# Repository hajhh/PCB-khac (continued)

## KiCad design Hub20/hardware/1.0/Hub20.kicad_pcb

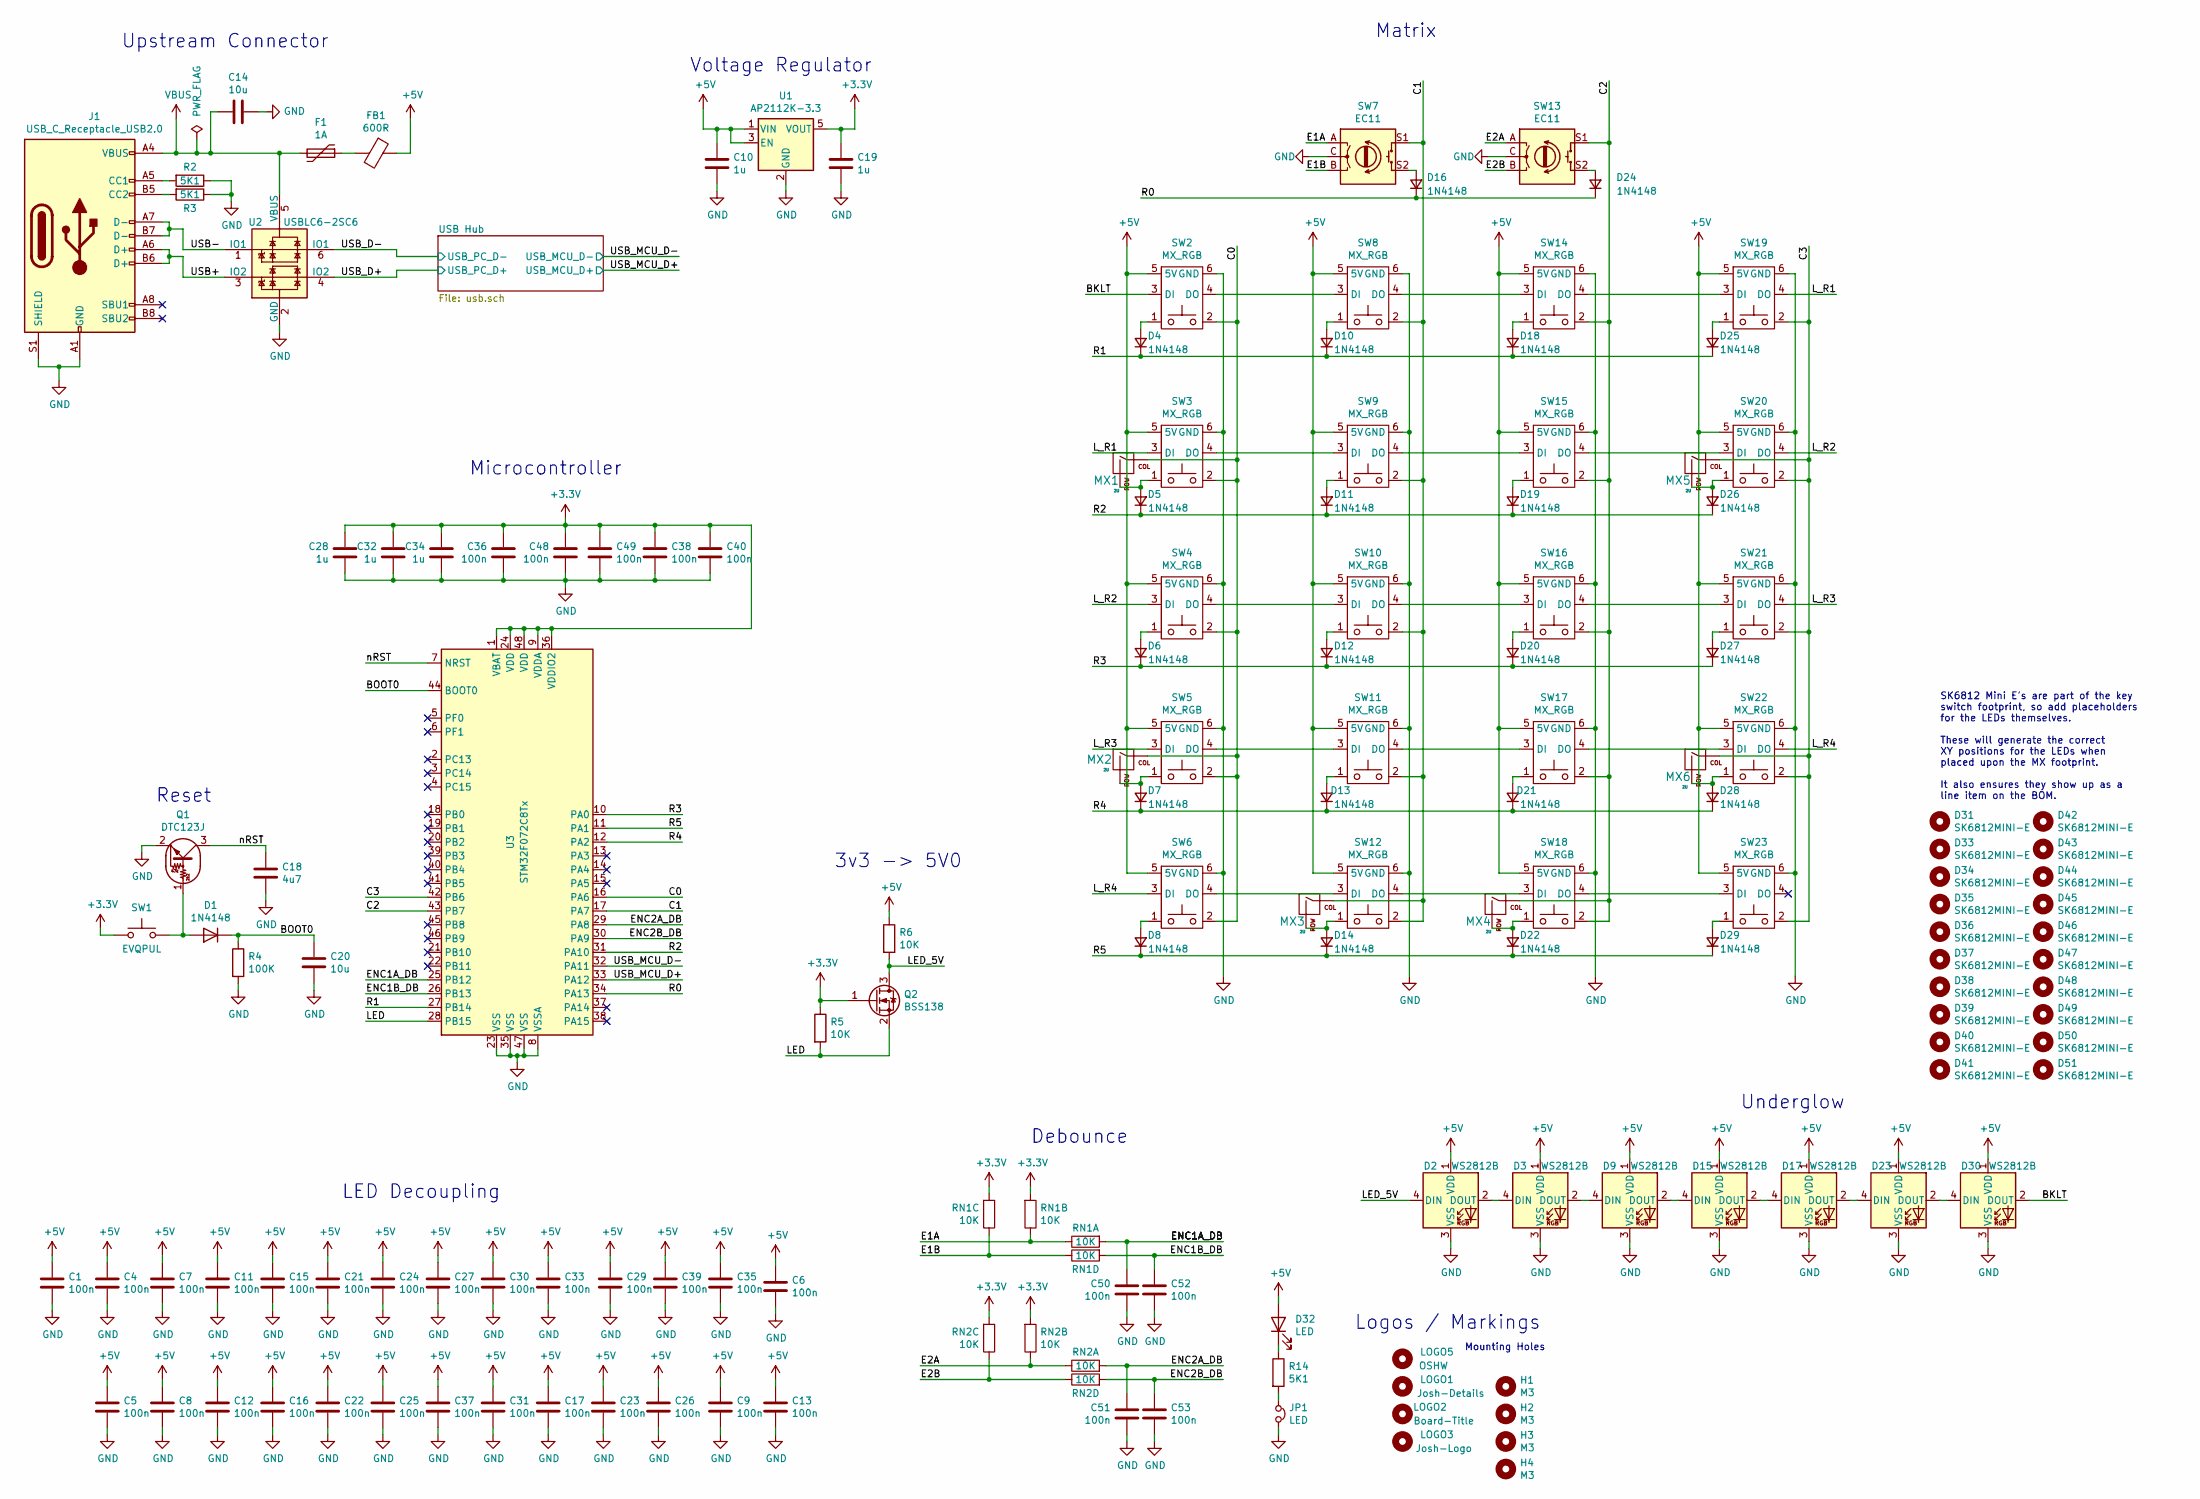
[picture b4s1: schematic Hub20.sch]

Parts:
C1, C4, C5, C6, C7, C8, C9, C11, C12, C13, C15, C16, C17, C21, C22, C23, C24, C25, C26, C27, C29, C30, C31, C33, C35, C36, C37, C38, C39, C40, C48, C49, C50, C51, C52, C53: 100n; C_0603_1608Metric; MPN CL10B104KB8NNNC; DigiKey 1276-1000-1-ND
C10, C19, C28, C32, C34: 1u; C_0603_1608Metric; MPN CL10A105MP8NNNC; DigiKey 1276-1866-1-ND
C14, C20: 10u; C_0603_1608Metric; MPN CL10A106MP8NNNC; DigiKey 1276-1871-1-ND
C18: 4u7; C_0603_1608Metric; MPN CL10A475MP8NNNC; DigiKey 1276-1905-1-ND
D1, D4, D5, D6, D7, D8, D10, D11, D12, D13, D14, D16, D18, D19, D20, D21, D22, D24, D25, D26, D27, D28, D29: 1N4148; D_SOD-123; MPN 1N4148W-7-F; DigiKey 1N4148W-FDICT-ND
D2, D3, D9, D15, D17, D23, D30: WS2812B; LED_WS2812B_PLCC4_5.0x5.0mm_P3.2mm; MPN WS2812B; DigiKey 1528-1104-ND
D31, D33, D34, D35, D36, D37, D38, D39, D40, D41, D42, D43, D44, D45, D46, D47, D48, D49, D50, D51: SK6812MINI-E; DUMMY_SK6812MINI-E; MPN SK6812MINI-E
D32: LED; LED_0603_1608Metric; MPN OSK40603C1E; LCSC C268294
F1: 1A; Fuse_0805_2012Metric; MPN 0805L100WR; DigiKey F2774CT-ND
FB1: 600R; Ferrite_Bead_0603; MPN BLM18KG601SN1D; DigiKey 490-5258-1-ND
H1, H2, H3, H4: M3; MountingHole_3.2mm_M3
J1: USB_C_Receptacle_USB2.0; USB_C_U262-161N-4BVC11; MPN U262-161N-4BVC11; LCSC C319148
JP1: LED; SolderJumper-2_P1.3mm_Bridged_RoundedPad1.0x1.5mm
LOGO1: Josh-Details; josh-details
LOGO2: Board-Title; board-title
LOGO3: Josh-Logo; josh-johnson-logo-11x2
LOGO5: OSHW; OSHW-Logo2_9.8x8mm_Mask
MX1, MX2: 2U; MXOnly-2U-NoLED-3PIN
MX3, MX4, MX5, MX6: 2U; MXOnly-2U-ReversedStabilizers-NoLED-3PIN
Q1: DTC123J; SOT-23; MPN DTC123JKAT146; DigiKey DTC123JKAT146CT-ND
Q2: BSS138; SOT-23; MPN BSS138; DigiKey BSS138CT-ND
R2, R3, R14: 5K1; R_0603_1608Metric; MPN CR0603-JW-512ELF; DigiKey 118-CR0603-JW-512ELFCT-ND
R4: 100K; R_0603_1608Metric; MPN CR0603-JW-104ELF; DigiKey CR0603-JW-104ELFCT-ND
R5, R6: 10K; R_0603_1608Metric; MPN CR0603-JW-103ELF; DigiKey CR0603-JW-103ELFCT-ND
RN1, RN2: 10K; R_Array_Convex_4x0603; MPN RAVF164DJT10K0; DigiKey RAVF164DJT10K0CT-ND
SW1: EVQPUL; Panasonic_EVQPUL_EVQPUC; MPN EVQ-PUL02K; DigiKey P10853SCT-ND
SW2, SW3, SW4, SW5, SW6, SW8, SW9, SW10, SW11, SW12, SW14, SW15, SW16, SW17, SW18, SW19, SW20, SW21, SW22, SW23: MX_RGB; MX_KEYSWITCH_RGB
SW7, SW13: EC11; RotaryEncoder_Alps_EC11E-Switch_Vertical_H20mm_CircularMoun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; MPN PEC11L-4120F-S0020; DigiKey PEC11L-4120F-S0020-ND
U1: AP2112K-3.3; SOT-23-5; MPN AP2112K-3.3TRG1; DigiKey AP2112K-3.3TRG1DICT-ND
U2: USBLC6-2SC6; SOT-23-6; MPN USBLC6-2SC6; DigiKey 497-5235-1-ND
U3: STM32F072C8Tx; LQFP-48_7x7mm_P0.5mm; MPN STM32F072C8T6; DigiKey 497-17359-1-ND

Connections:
+3V3: C19.1, C28.1, C32.1, C34.1, C36.1, C38.1, C40.1, C48.1, C49.1, Q2.1 (G), R5.1, RN1.2, RN1.3, RN2.2, RN2.3, SW1.1, U1.5 (VOUT), U3.1 (VBAT), U3.9 (VDDA), U3.24 (VDD), U3.36 (VDDIO2), U3.48 (VDD)
/BKLT: D30.2 (DOUT), SW2.3 (DI)
/BOOT0: C20.1, D1.1 (K), R4.1, U3.44 (BOOT0)
/C0: MX1.1 (COL), MX2.1 (COL), SW2.2, SW3.2, SW4.2, SW5.2, SW6.2, U3.16 (PA6)
/C1: MX3.1 (COL), SW7.S1, SW8.2, SW9.2, SW10.2, SW11.2, SW12.2, U3.17 (PA7)
/C2: MX4.1 (COL), SW13.S1, SW14.2, SW15.2, SW16.2, SW17.2, SW18.2, U3.43 (PB7)
/C3: MX5.1 (COL), MX6.1 (COL), SW19.2, SW20.2, SW21.2, SW22.2, SW23.2, U3.42 (PB6)
/E1A: RN1.5, RN1.6, SW7.A
/E1B: RN1.7, RN1.8, SW7.B
/E2A: RN2.5, RN2.6, SW13.A
/E2B: RN2.7, RN2.8, SW13.B
/ENC1A_DB: C50.1, RN1.4, U3.25 (PB12)
/ENC1B_DB: C52.1, RN1.1, U3.26 (PB13)
/ENC2A_DB: C51.1, RN2.4, U3.29 (PA8)
/ENC2B_DB: C53.1, RN2.1, U3.30 (PA9)
/LED: Q2.2 (S), R5.2, U3.28 (PB15)
/LED_5V: D2.4 (DIN), Q2.3 (D), R6.2
/L_R1: SW3.3 (DI), SW19.4 (DO)
/L_R2: SW4.3 (DI), SW20.4 (DO)
/L_R3: SW5.3 (DI), SW21.4 (DO)
/L_R4: SW6.3 (DI), SW22.4 (DO)
/R0: D16.1 (K), D24.1 (K), U3.34 (PA13)
/R1: D4.1 (K), D10.1 (K), D18.1 (K), D25.1 (K), U3.27 (PB14)
/R2: D5.1 (K), D11.1 (K), D19.1 (K), D26.1 (K), U3.31 (PA10)
/R3: D6.1 (K), D12.1 (K), D20.1 (K), D27.1 (K), U3.10 (PA0)
/R4: D7.1 (K), D13.1 (K), D21.1 (K), D28.1 (K), U3.12 (PA2)
/R5: D8.1 (K), D14.1 (K), D22.1 (K), D29.1 (K), U3.11 (PA1)
/USB+: J1.A6 (D+), J1.B6 (D+), U2.3 (IO2)
/USB-: J1.A7 (D-), J1.B7 (D-), U2.1 (IO1)
/USB_D+: U2.4 (IO2); also elsewhere on the board
/USB_D-: U2.6 (IO1); also elsewhere on the board
/USB_MCU_D+: U3.33 (PA12); also elsewhere on the board
/USB_MCU_D-: U3.32 (PA11); also elsewhere on the board
GND: C1.2, C4.2, C5.2, C6.2, C7.2, C8.2, C9.2, C10.2, C11.2, C12.2, C13.2, C14.2, C15.2, C16.2, C17.2, C18.2, C19.2, C20.2, C21.2, C22.2, C23.2, C24.2, C25.2, C26.2, C27.2, C28.2, C29.2, C30.2, C31.2, C32.2, C33.2, C34.2, C35.2, C36.2, C37.2, C38.2, C39.2, C40.2, C48.2, C49.2, C50.2, C51.2, C52.2, C53.2, D2.3 (VSS), D3.3 (VSS), D9.3 (VSS), D15.3 (VSS), D17.3 (VSS), D23.3 (VSS), D30.3 (VSS), J1.A1 (GND), J1.A12 (GND), J1.B1 (GND), J1.B12 (GND), J1.S1 (SHIELD), JP1.2, Q1.2 (E), R2.1, R3.1, R4.2, SW2.6 (GND), SW3.6 (GND), SW4.6 (GND), SW5.6 (GND), SW6.6 (GND), SW7.C, SW8.6 (GND), SW9.6 (GND), SW10.6 (GND), SW11.6 (GND), SW12.6 (GND), SW13.C, SW14.6 (GND), SW15.6 (GND), SW16.6 (GND), SW17.6 (GND), SW18.6 (GND), SW19.6 (GND), SW20.6 (GND), SW21.6 (GND), SW22.6 (GND), SW23.6 (GND), U1.2 (GND), U2.2 (GND), U3.8 (VSSA), U3.23 (VSS), U3.35 (VSS), U3.47 (VSS); also elsewhere on the board
unnamed: D1.2 (A), Q1.1 (B), SW1.2
unnamed: D2.2 (DOUT), D3.4 (DIN)
unnamed: D3.2 (DOUT), D9.4 (DIN)
unnamed: D4.2 (A), SW2.1
unnamed: D5.2 (A), MX1.2 (ROW), SW3.1
unnamed: D6.2 (A), SW4.1
unnamed: D7.2 (A), MX2.2 (ROW), SW5.1
unnamed: D8.2 (A), SW6.1
unnamed: D10.2 (A), SW8.1
unnamed: D11.2 (A), SW9.1
unnamed: D12.2 (A), SW10.1
unnamed: D13.2 (A), SW11.1
unnamed: D14.2 (A), MX3.2 (ROW), SW12.1
unnamed: D15.2 (DOUT), D17.4 (DIN)
unnamed: D9.2 (DOUT), D15.4 (DIN)
unnamed: D16.2 (A), SW7.S2
unnamed: D17.2 (DOUT), D23.4 (DIN)
unnamed: D18.2 (A), SW14.1
unnamed: D19.2 (A), SW15.1
unnamed: D20.2 (A), SW16.1
unnamed: D21.2 (A), SW17.1
unnamed: D22.2 (A), MX4.2 (ROW), SW18.1
unnamed: D23.2 (DOUT), D30.4 (DIN)
unnamed: D24.2 (A), SW13.S2
unnamed: D25.2 (A), SW19.1
unnamed: D26.2 (A), MX5.2 (ROW), SW20.1
unnamed: D27.2 (A), SW21.1
unnamed: D28.2 (A), MX6.2 (ROW), SW22.1
unnamed: D29.2 (A), SW23.1
unnamed: D32.1 (K), R14.1
unnamed: J1.A5 (CC1), R2.2
unnamed: J1.B5 (CC2), R3.2
unnamed: JP1.1, R14.2
unnamed: SW2.4 (DO), SW8.3 (DI)
unnamed: SW3.4 (DO), SW9.3 (DI)
unnamed: SW4.4 (DO), SW10.3 (DI)
unnamed: SW10.4 (DO), SW16.3 (DI)
unnamed: SW5.4 (DO), SW11.3 (DI)
unnamed: SW11.4 (DO), SW17.3 (DI)
unnamed: SW6.4 (DO), SW12.3 (DI)
unnamed: SW12.4 (DO), SW18.3 (DI)
unnamed: SW8.4 (DO), SW14.3 (DI)
unnamed: SW14.4 (DO), SW19.3 (DI)
unnamed: SW9.4 (DO), SW15.3 (DI)
unnamed: SW15.4 (DO), SW20.3 (DI)
unnamed: SW16.4 (DO), SW21.3 (DI)
unnamed: SW17.4 (DO), SW22.3 (DI)
unnamed: SW18.4 (DO), SW23.3 (DI)
VBUS: C14.1, F1.2, J1.A4 (VBUS), J1.A9 (VBUS), J1.B4 (VBUS), J1.B9 (VBUS), U2.5 (VBUS)

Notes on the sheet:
Logos / Markings
Mounting Holes
Voltage Regulator
Upstream Connector
Reset
Debounce
Underglow
LED Decoupling
Matrix
Microcontroller
3v3 -> 5V0
SK6812 Mini E's are part of the key switch footprint, so add placeholders for the LEDs themselves. These will generate the correct XY positions for the LEDs when placed upon the MX footprint. It also ensures they show up as a line item on the BOM.

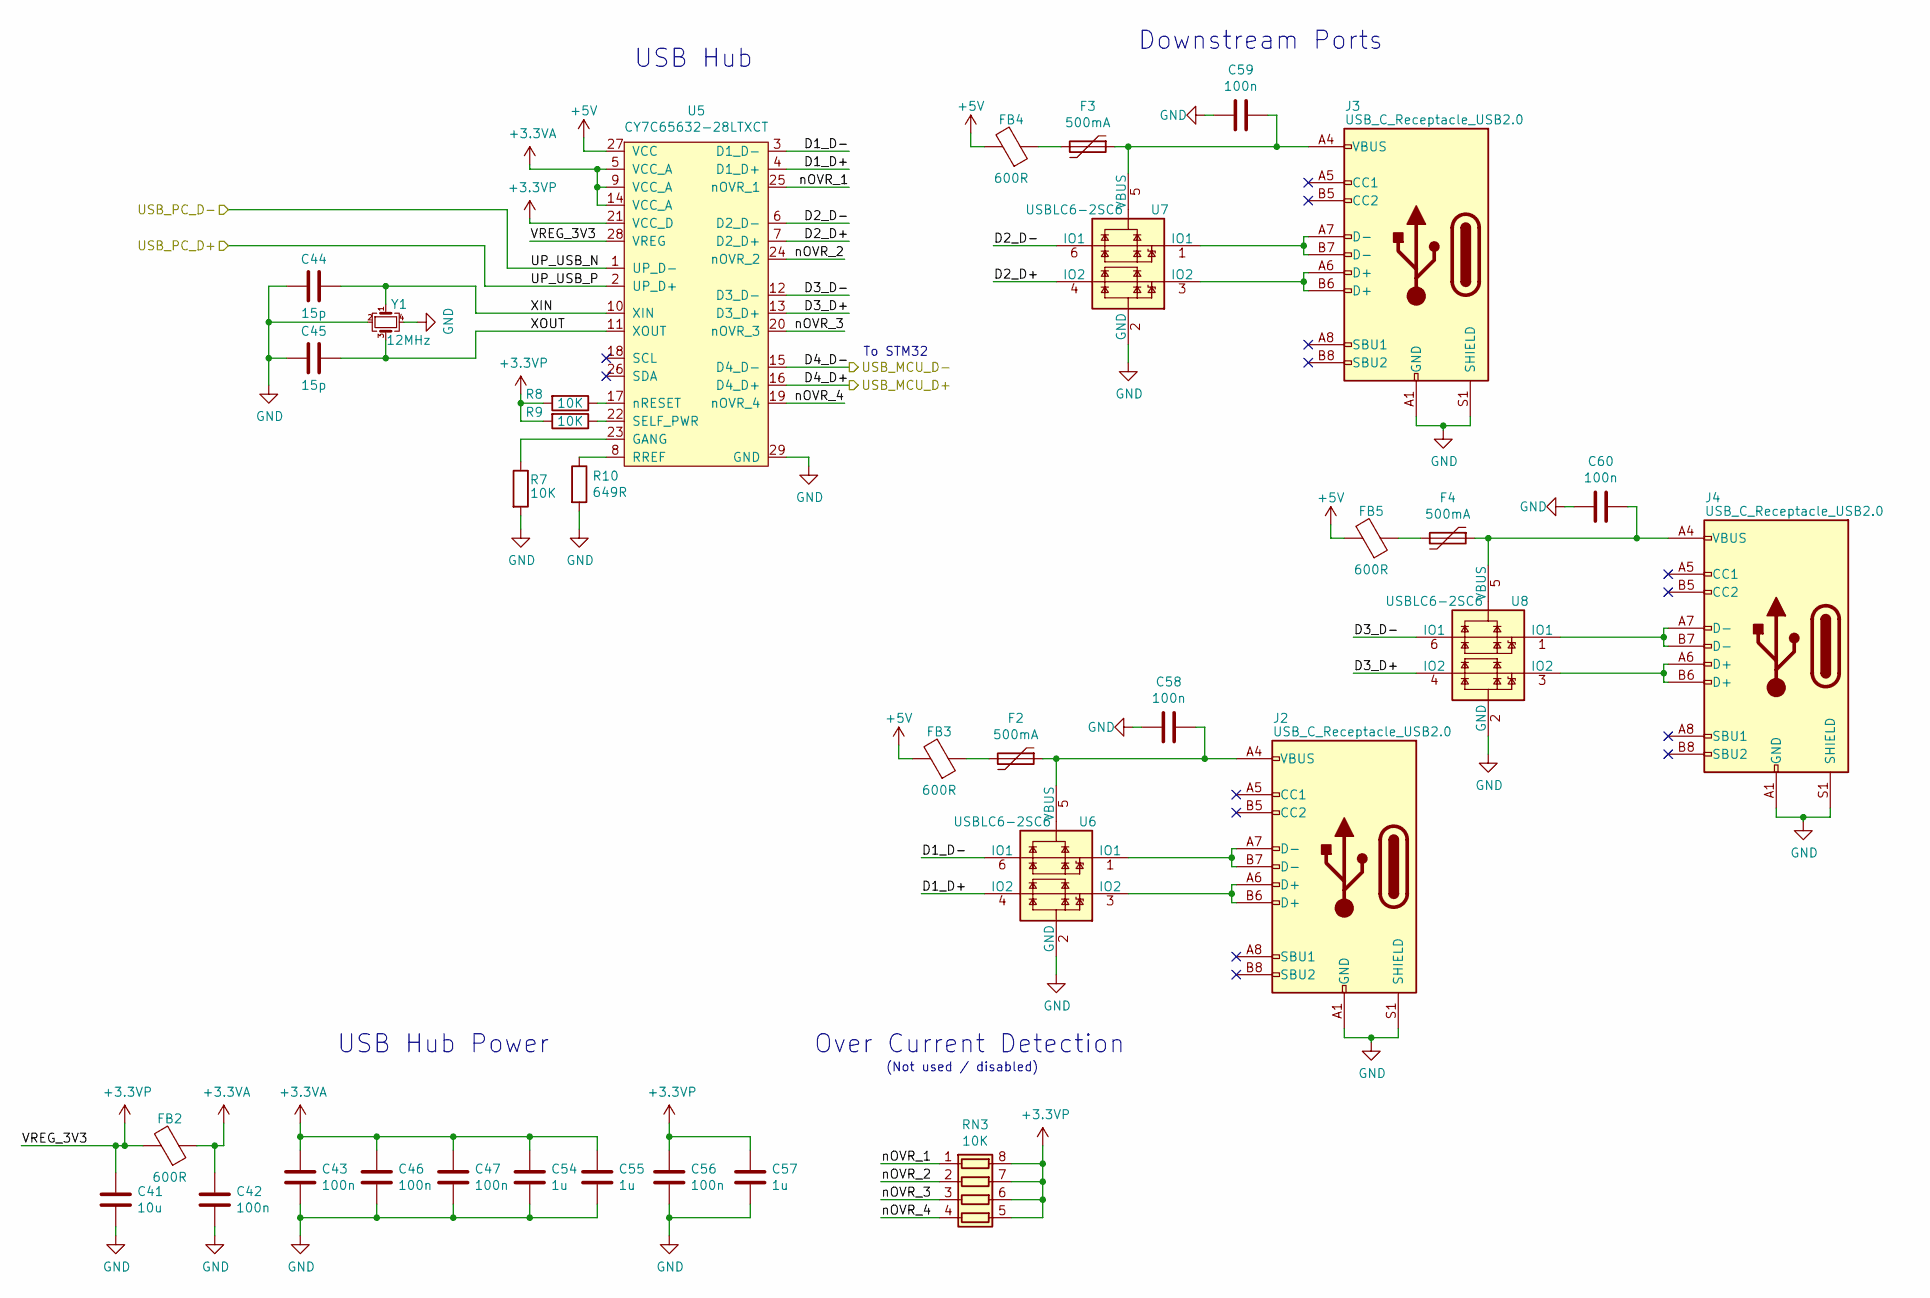
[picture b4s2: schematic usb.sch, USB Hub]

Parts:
C17, C18: 15p; C_0603_1608Metric; MPN CL10C150JB8NNNC; DigiKey 1276-1296-2-ND
C41: 10u; C_0603_1608Metric; MPN CL10A106MP8NNNC; DigiKey 1276-1871-1-ND
C42, C43, C46, C47, C56, C58, C59, C60: 100n; C_0603_1608Metric; MPN CL10B104KB8NNNC; DigiKey 1276-1000-1-ND
C54, C55, C57: 1u; C_0603_1608Metric; MPN CL10A105MP8NNNC; DigiKey 1276-1866-1-ND
F2, F3, F4: 500mA; Fuse_0805_2012Metric; MPN 0805L050WR; DigiKey F2772CT-ND
FB1, FB2, FB3, FB4: 600R; Ferrite_Bead_0603; MPN BLM18KG601SN1D; LCSC C85833
J2, J3, J4: USB_C_Receptacle_USB2.0; USB_C_U262-161N-4BVC11; MPN U262-161N-4BVC11; LCSC C319148
R7, R8, R9: 10K; R_0603_1608Metric; MPN CR0603-JW-103ELF; DigiKey CR0603-JW-103ELFCT-ND
R10: 649R; R_0603_1608Metric; MPN MCR03ERTF6490; DigiKey RHM649CFCT-ND
RN3: 10K; R_Array_Convex_4x0603; MPN RAVF164DJT10K0; DigiKey RAVF164DJT10K0CT-ND
U5: CY7C65632-28LTXCT; QFN-28-1EP_5x5mm_P0.5mm_EP3.35x3.35mm_ThermalVias; MPN CY7C65632-28LTXCT; LCSC C466886
U6, U7, U8: USBLC6-2SC6; SOT-23-6; MPN USBLC6-2SC6; DigiKey 497-5235-1-ND
Y2: 12MHz; Crystal_SMD_3225-4Pin_3.2x2.5mm; MPN ABM8-12.000MHZ-12-B1U-T; LCSC C164041

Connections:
/USB Hub/D1_D+: U5.4 (D1_D+), U6.4 (IO2)
/USB Hub/D1_D-: U5.3 (D1_D-), U6.6 (IO1)
/USB Hub/D2_D+: U5.7 (D2_D+), U7.4 (IO2)
/USB Hub/D2_D-: U5.6 (D2_D-), U7.6 (IO1)
/USB Hub/D3_D+: U5.13 (D3_D+), U8.4 (IO2)
/USB Hub/D3_D-: U5.12 (D3_D-), U8.6 (IO1)
/USB Hub/nOVR_1: RN3.1 (R1.1), U5.25 (nOVR_1)
/USB Hub/nOVR_2: RN3.2 (R2.1), U5.24 (nOVR_2)
/USB Hub/nOVR_3: RN3.3 (R3.1), U5.20 (nOVR_3)
/USB Hub/nOVR_4: RN3.4 (R4.1), U5.19 (nOVR_4)
/USB_D+: U5.2 (UP_D+); also elsewhere on the board
/USB_D-: U5.1 (UP_D-); also elsewhere on the board
/USB_MCU_D+: U5.16 (D4_D+); also elsewhere on the board
/USB_MCU_D-: U5.15 (D4_D-); also elsewhere on the board
GND: C17.2, C18.2, C41.2, C42.2, C43.2, C46.2, C47.2, C54.2, C55.2, C56.2, C57.2, C58.2, C59.2, C60.2, J2.A1 (GND), J2.A12 (GND), J2.B1 (GND), J2.B12 (GND), J2.S1 (SHIELD), J3.A1 (GND), J3.A12 (GND), J3.B1 (GND), J3.B12 (GND), J3.S1 (SHIELD), J4.A1 (GND), J4.A12 (GND), J4.B1 (GND), J4.B12 (GND), J4.S1 (SHIELD), R7.2, R10.2, U5.29 (GND), U6.2 (GND), U7.2 (GND), U8.2 (GND); also elsewhere on the board
unnamed: C58.1, F2.1, J2.A4 (VBUS), J2.A9 (VBUS), J2.B4 (VBUS), J2.B9 (VBUS), U6.5 (VBUS)
unnamed: C59.1, F3.1, J3.A4 (VBUS), J3.A9 (VBUS), J3.B4 (VBUS), J3.B9 (VBUS), U7.5 (VBUS)
unnamed: C60.1, F4.1, J4.A4 (VBUS), J4.A9 (VBUS), J4.B4 (VBUS), J4.B9 (VBUS), U8.5 (VBUS)
unnamed: F2.2, FB3.1
unnamed: F3.2, FB4.1
unnamed: J2.A6 (D+), J2.B6 (D+), U6.3 (IO2)
unnamed: J2.A7 (D-), J2.B7 (D-), U6.1 (IO1)
unnamed: J3.A6 (D+), J3.B6 (D+), U7.3 (IO2)
unnamed: J3.A7 (D-), J3.B7 (D-), U7.1 (IO1)
unnamed: J4.A6 (D+), J4.B6 (D+), U8.3 (IO2)
unnamed: J4.A7 (D-), J4.B7 (D-), U8.1 (IO1)
unnamed: R7.1, U5.23 (GANG)
unnamed: R8.1, U5.17 (nRESET)
unnamed: R9.1, U5.22 (SELF_PWR)
unnamed: R10.1, U5.8 (RREF)

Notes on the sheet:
USB Hub
USB Hub Power
Over Current Detection
(Not used / disabled)
Downstream Ports
To STM32

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
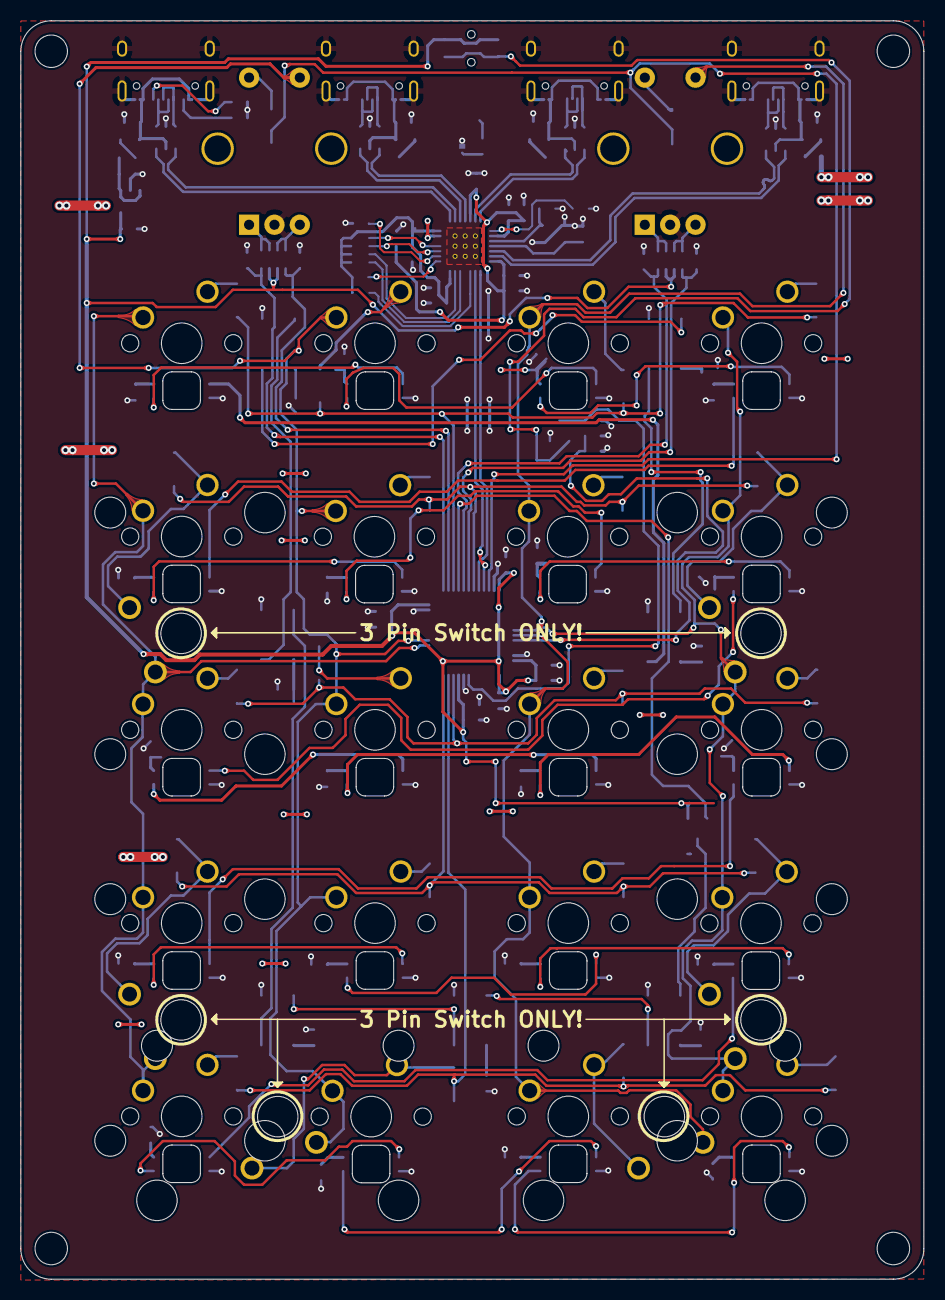
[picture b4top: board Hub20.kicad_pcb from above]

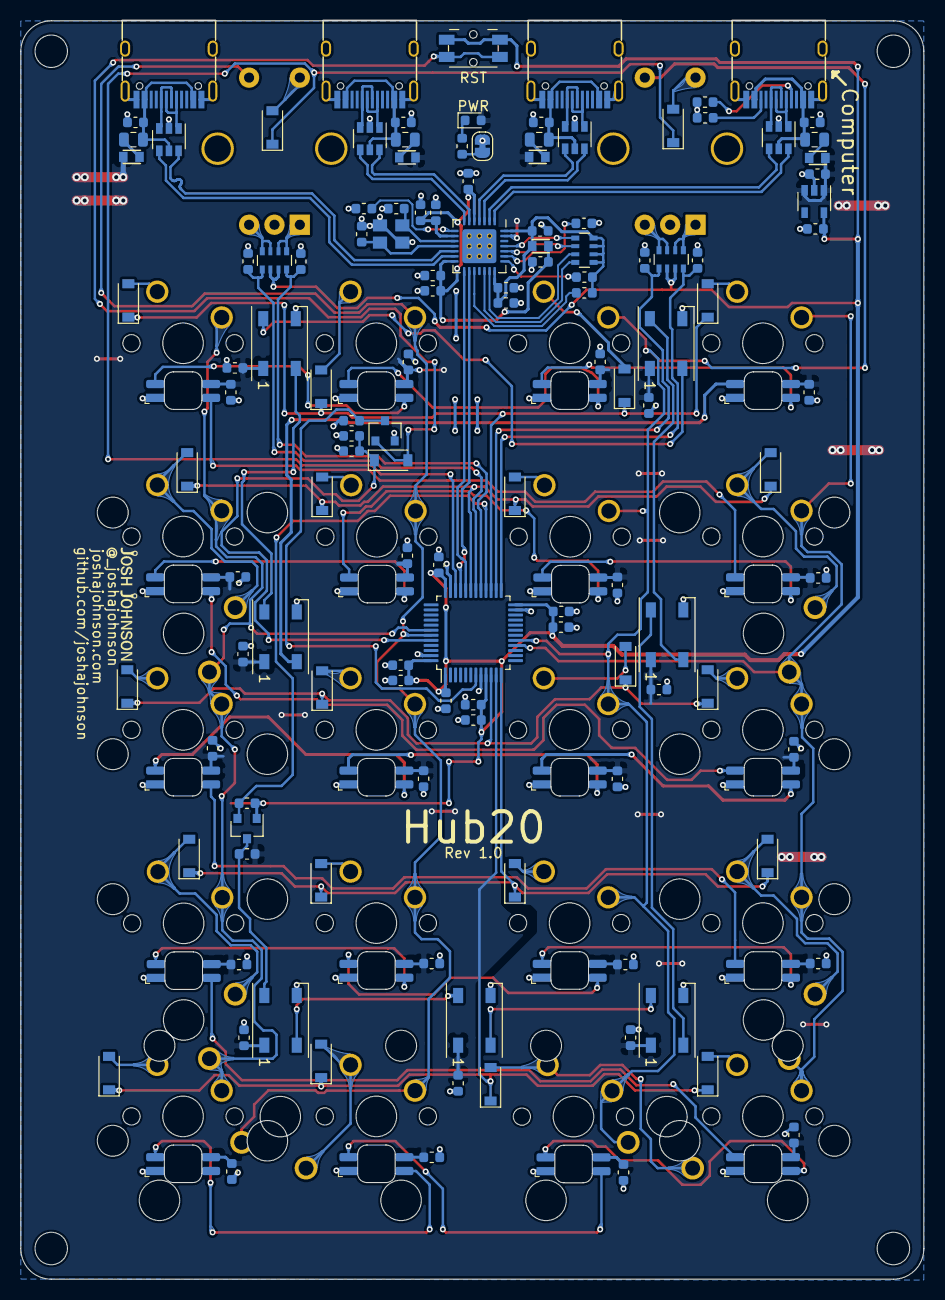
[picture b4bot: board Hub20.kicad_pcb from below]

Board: 2 copper layers, 89.0 x 124.0 mm, 183 parts (151 on the bottom side), 116 nets.

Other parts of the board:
C44, C45: 15p; C_0603_1608Metric
FB5: 600R; Ferrite_Bead_0603
Y1: 12MHz; Crystal_SMD_3225-4Pin_3.2x2.5mm

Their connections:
GND: C44.2, C45.2, Y1.2, Y1.4; also elsewhere on the board

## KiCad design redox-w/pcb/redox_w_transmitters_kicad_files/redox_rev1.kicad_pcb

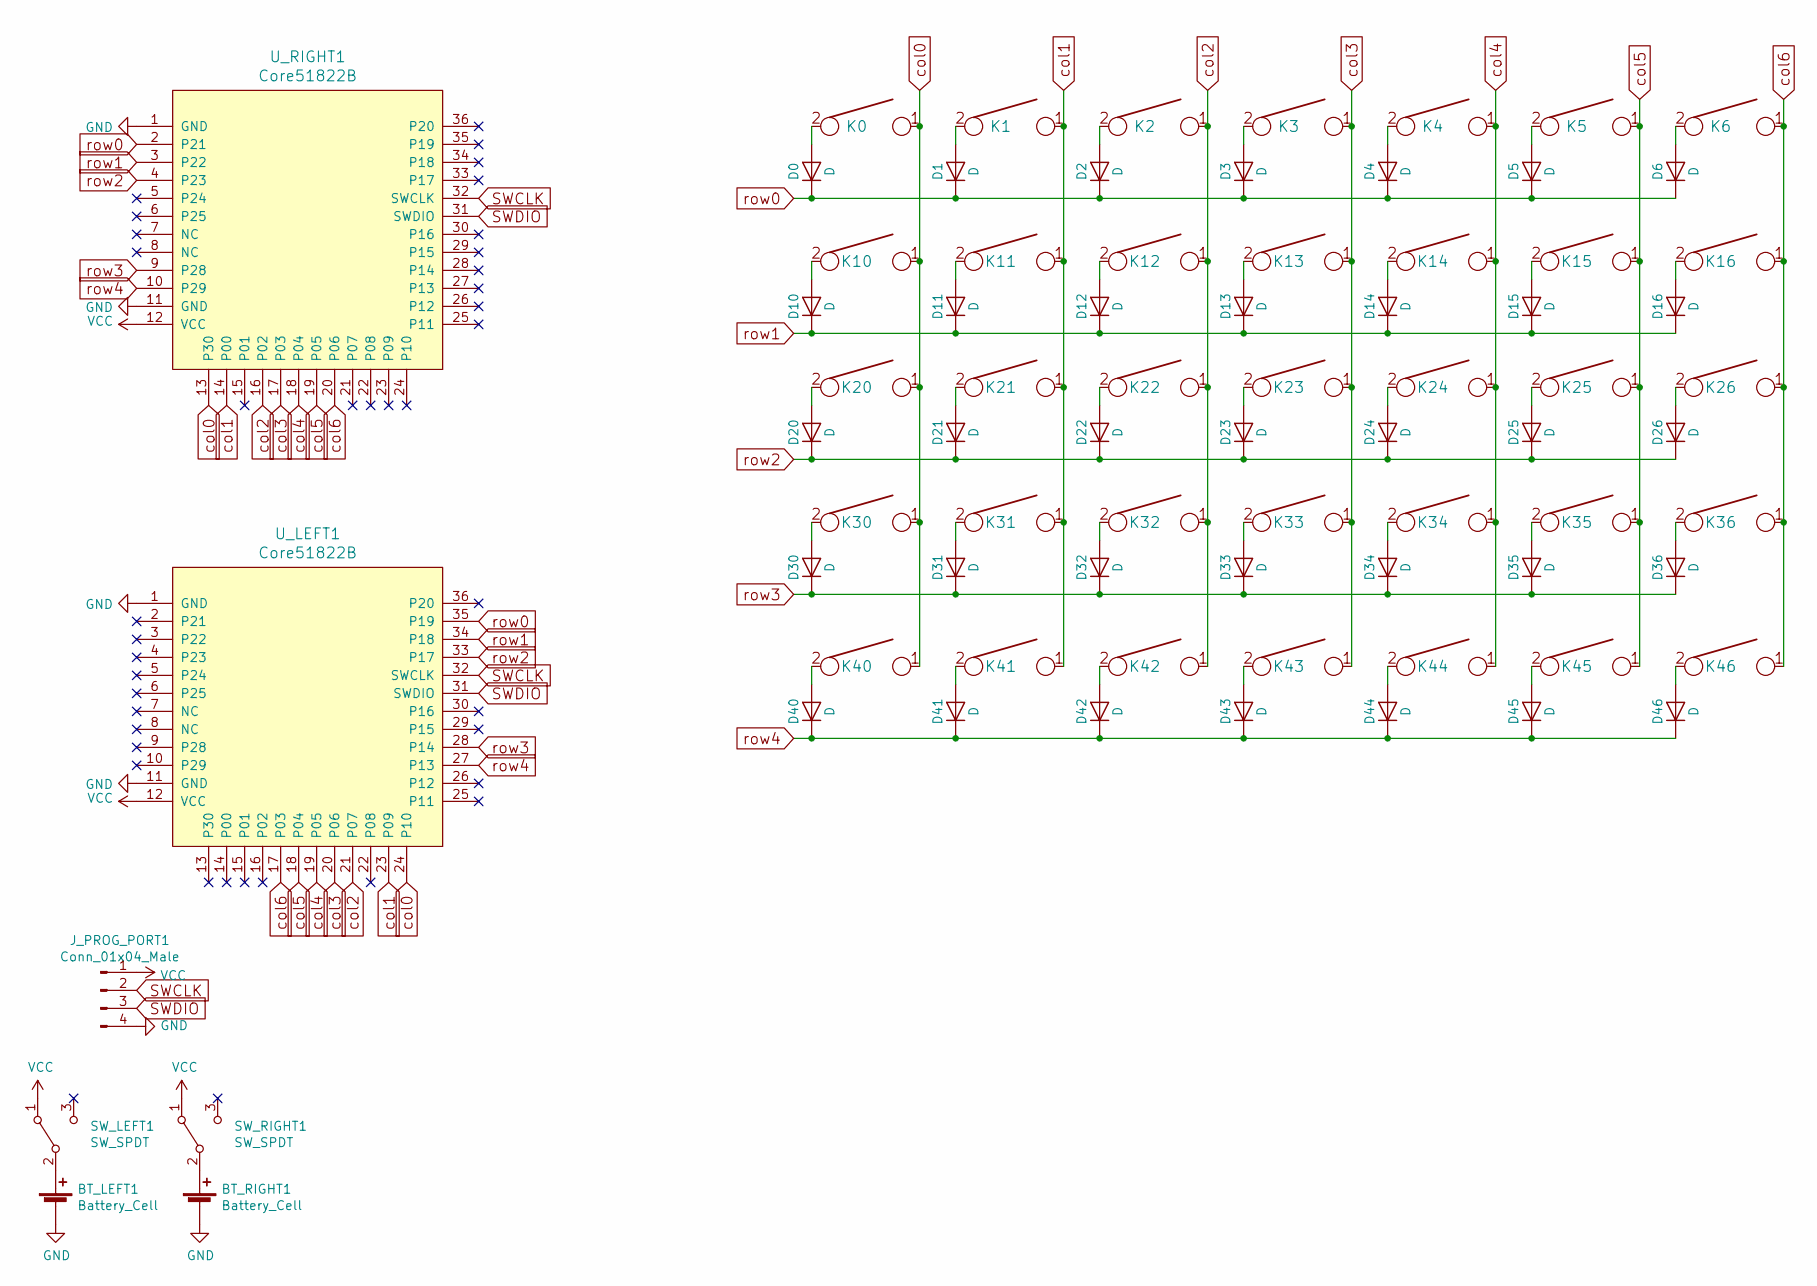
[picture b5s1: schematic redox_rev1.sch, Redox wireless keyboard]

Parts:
BT_LEFT1: Battery_Cell; BatteryHolder_Keystone_3034_1x20mm
BT_RIGHT1: Battery_Cell; BatteryHolder_Keystone_3034_1x20mm
D0, D1, D2, D3, D4, D5, D6, D10, D11, D12, D13, D14, D15, D16, D20, D21, D22, D23, D24, D25, D26, D30, D31, D32, D33, D34, D35, D36, D40, D41, D42, D43, D44, D45, D46: D; Diode-dual
J_PROG_PORT1: Conn_01x04_Male; PinHeader_1x04_P2.54mm_Vertical
K0, K1, K2, K3, K4, K5, K6, K10, K11, K12, K13, K14, K15, K16, K20, K21, K22, K23, K24, K25, K26, K30, K31, K32, K33, K34, K35, K36, K40, K41, K42, K43, K44, K45, K46: KEYSW; Mx_Alps_100-dualside
SW_LEFT1: SW_SPDT; SW_SPDT_CK-JS102011SAQN
SW_RIGHT1: SW_SPDT; SW_SPDT_CK-JS102011SAQN
U_LEFT1: Core51822B; YJ-14015-Modul
U_RIGHT1: Core51822B; YJ-14015-Modul

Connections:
GND: BT_LEFT1.2 (-), BT_RIGHT1.2 (-), J_PROG_PORT1.4, U_LEFT1.1 (GND), U_LEFT1.11 (GND), U_RIGHT1.1 (GND), U_RIGHT1.11 (GND)
unnamed: BT_LEFT1.1 (+), SW_LEFT1.2 (B)
unnamed: BT_RIGHT1.1 (+), SW_RIGHT1.2 (B)
unnamed: D0.2 (A), K0.2
unnamed: D1.2 (A), K1.2
unnamed: D2.2 (A), K2.2
unnamed: D3.2 (A), K3.2
unnamed: D4.2 (A), K4.2
unnamed: D5.2 (A), K5.2
unnamed: D6.2 (A), K6.2
unnamed: D10.2 (A), K10.2
unnamed: D11.2 (A), K11.2
unnamed: D12.2 (A), K12.2
unnamed: D13.2 (A), K13.2
unnamed: D14.2 (A), K14.2
unnamed: D15.2 (A), K15.2
unnamed: D16.2 (A), K16.2
unnamed: D20.2 (A), K20.2
unnamed: D21.2 (A), K21.2
unnamed: D22.2 (A), K22.2
unnamed: D23.2 (A), K23.2
unnamed: D24.2 (A), K24.2
unnamed: D25.2 (A), K25.2
unnamed: D26.2 (A), K26.2
unnamed: D30.2 (A), K30.2
unnamed: D31.2 (A), K31.2
unnamed: D32.2 (A), K32.2
unnamed: D33.2 (A), K33.2
unnamed: D34.2 (A), K34.2
unnamed: D35.2 (A), K35.2
unnamed: D36.2 (A), K36.2
unnamed: D40.2 (A), K40.2
unnamed: D41.2 (A), K41.2
unnamed: D42.2 (A), K42.2
unnamed: D43.2 (A), K43.2
unnamed: D44.2 (A), K44.2
unnamed: D45.2 (A), K45.2
unnamed: D46.2 (A), K46.2
SWCLK: J_PROG_PORT1.2, U_LEFT1.32 (SWCLK), U_RIGHT1.32 (SWCLK)
SWDIO: J_PROG_PORT1.3, U_LEFT1.31 (SWDIO), U_RIGHT1.31 (SWDIO)
VCC: J_PROG_PORT1.1, SW_LEFT1.1 (A), SW_RIGHT1.1 (A), U_LEFT1.12 (VCC), U_RIGHT1.12 (VCC)
col0: K0.1, K10.1, K20.1, K30.1, K40.1, U_LEFT1.24 (P10), U_RIGHT1.13 (P30)
col1: K1.1, K11.1, K21.1, K31.1, K41.1, U_LEFT1.23 (P09), U_RIGHT1.14 (P00)
col2: K2.1, K12.1, K22.1, K32.1, K42.1, U_LEFT1.21 (P07), U_RIGHT1.16 (P02)
col3: K3.1, K13.1, K23.1, K33.1, K43.1, U_LEFT1.20 (P06), U_RIGHT1.17 (P03)
col4: K4.1, K14.1, K24.1, K34.1, K44.1, U_LEFT1.19 (P05), U_RIGHT1.18 (P04)
col5: K5.1, K15.1, K25.1, K35.1, K45.1, U_LEFT1.18 (P04), U_RIGHT1.19 (P05)
col6: K6.1, K16.1, K26.1, K36.1, K46.1, U_LEFT1.17 (P03), U_RIGHT1.20 (P06)
row0: D0.1 (K), D1.1 (K), D2.1 (K), D3.1 (K), D4.1 (K), D5.1 (K), D6.1 (K), U_LEFT1.35 (P19), U_RIGHT1.2 (P21)
row1: D10.1 (K), D11.1 (K), D12.1 (K), D13.1 (K), D14.1 (K), D15.1 (K), D16.1 (K), U_LEFT1.34 (P18), U_RIGHT1.3 (P22)
row2: D20.1 (K), D21.1 (K), D22.1 (K), D23.1 (K), D24.1 (K), D25.1 (K), D26.1 (K), U_LEFT1.33 (P17), U_RIGHT1.4 (P23)
row3: D30.1 (K), D31.1 (K), D32.1 (K), D33.1 (K), D34.1 (K), D35.1 (K), D36.1 (K), U_LEFT1.28 (P14), U_RIGHT1.9 (P28)
row4: D40.1 (K), D41.1 (K), D42.1 (K), D43.1 (K), D44.1 (K), D45.1 (K), D46.1 (K), U_LEFT1.27 (P13), U_RIGHT1.10 (P29)

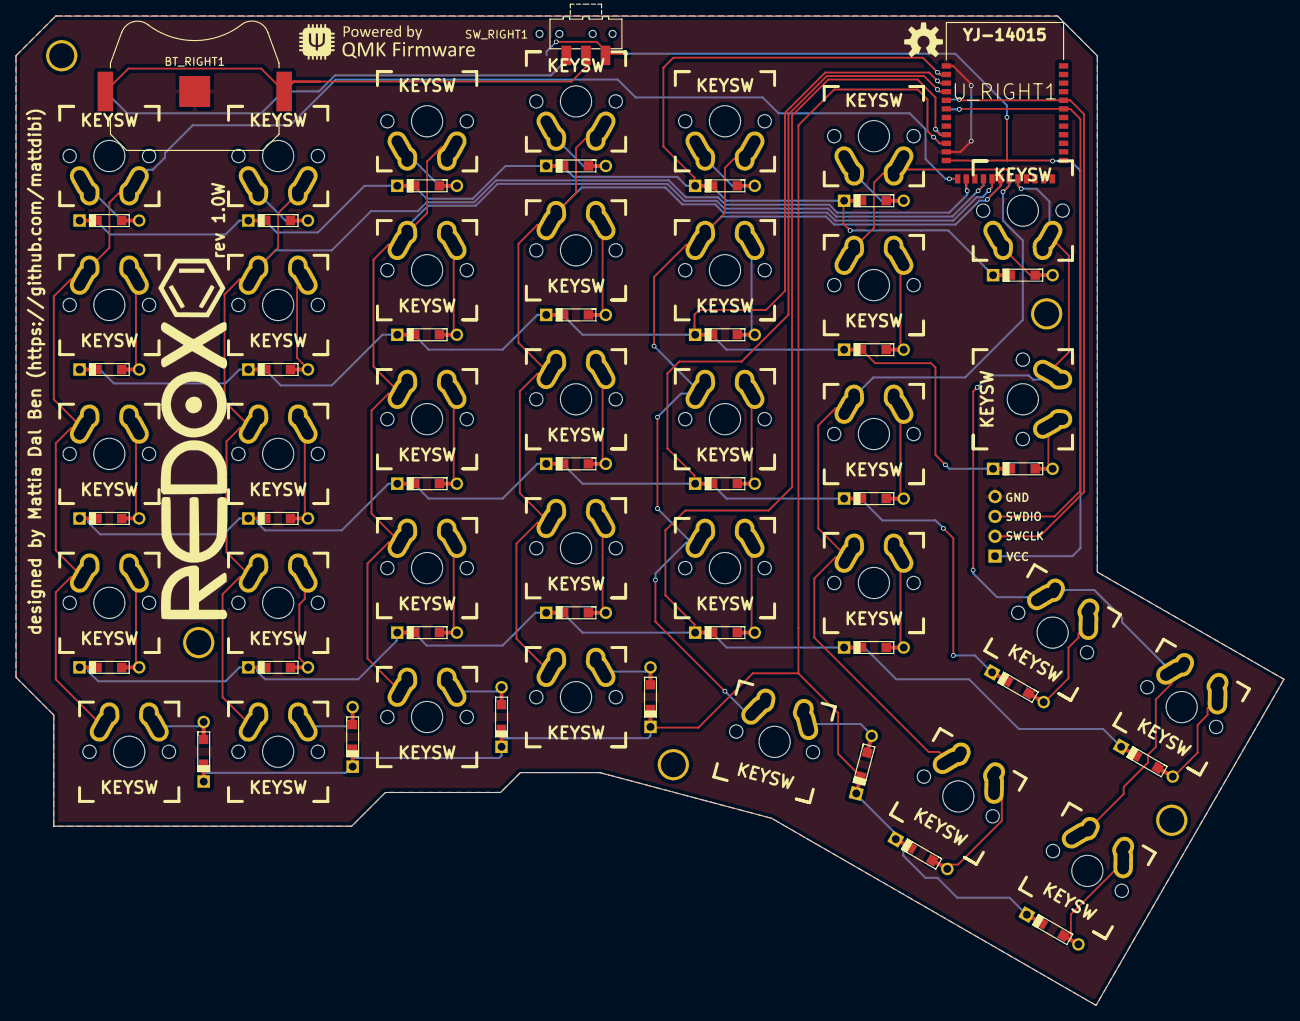
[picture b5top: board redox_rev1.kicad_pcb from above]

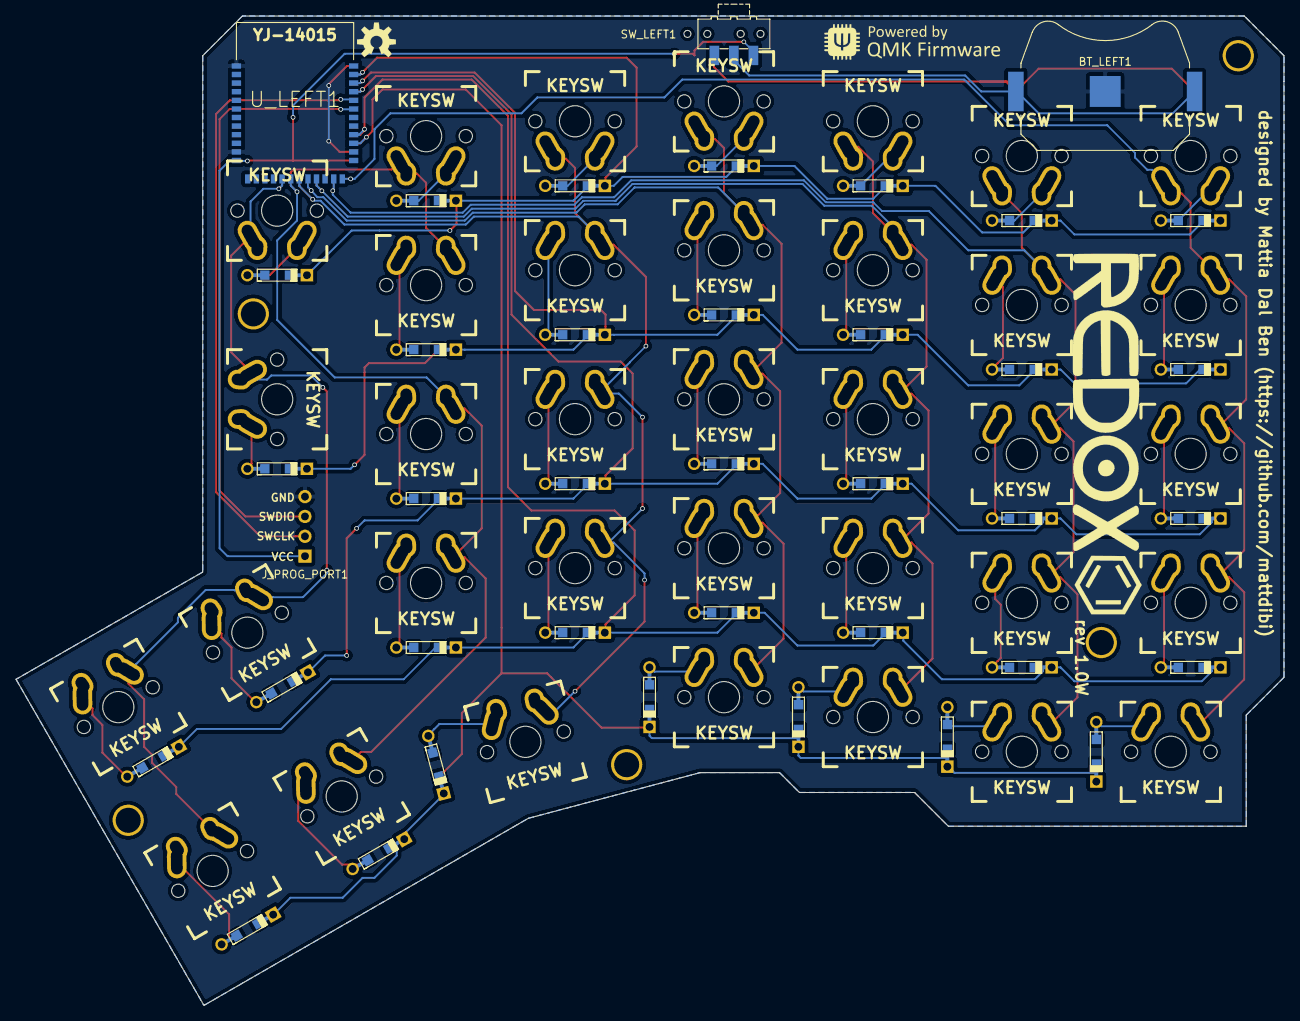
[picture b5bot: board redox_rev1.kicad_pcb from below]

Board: 2 copper layers, 162.2 x 126.5 mm, 82 parts (4 on the bottom side), 53 nets.

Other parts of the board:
HOLE_M3, HOLE_M3#2, HOLE_M3#3, HOLE_M3#4, HOLE_M3#5: VAL**; HOLE_M3
